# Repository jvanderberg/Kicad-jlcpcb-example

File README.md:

# JLCPCB KiCad Integration Example

This repository is a two layer 5V DC-DC power supply, created in KiCad and designed to integrate with JLCPCB. The power supply was just a test board I created, it should not be used for anything meaningful, but you could use this project as a template for new projects or just to test submitting to JCLPCB, and just delete the board unordered when you are done.

## Installing Libraries/Plugins

To get your local KiCad installation setup properly, open the Plugin and Content Manager.

1. Install the 'Fabrication Toolkit' Plugin from the KiCad official repository.

2. Install the 'impartGUI' Plugin from the KiCad official repository. Yes, that likely should be 'import GUI', but it's not.

3. In the Plugin and Content Manager, click the 'Manage...' button and add a new Repository with the URL: https://raw.githubusercontent.com/CDFER/cd_fer-kicad-repository/main/repository.json

4. Select 'CD_FER's KiCad repository' from the Repository drop down, select the 'Library' tab below, and then install 'JLCPCB KiCad Library'. Then 'Apply Changes'.

## Using 'JLCPCB KiCad Library'

'JLCPCB KiCad Library' integrates itself into KiCad as provider of 3rd party symbols and matching footprints for all of the JLCPCB basic and preferred parts and for some selected popular extended parts. Basic parts are the parts that don't cost extra month for 'Economic' PCB assembly. To use this library:

1. Open the schematic editor and select 'Place | Place Symbols'

2. Search for a part, for example '100nf', '10kΩ', 'jlcpcb schottky'. If you want to browse all of the JLCPCB parts search for 'jlcpcb'

3. Select a matching part from the 'PCM_JLCPCB\*' folder. The name of the folder will vary based on the type of part.

I tend to use this mostly for passive resistors and capacitors and use impartGUI for everything else.

## impartGUI Configuration

If you use impartGUI to import LCSC part numbers (LCSC is the JLCPCB part supplier), you will need to tell KiCad where to find the footprints and symbols that impartGUI manages.

1. From the schematic editor, select 'Preferences | Manage Symbol Libraries' and add either a Global or Project Specific library that points to the .kicad_sym file that impart GUI downloaded. For example, in this project, it's a project specific directory, with a path ${KIPRJMOD}/LCSC/EasyEDA.kicad_sym.

2. From the PCB editor, select 'Preferences | Manage Footprint Libraries' and add either a Global or a Project Specific Library that points to the EasyEDA.pretty directory that impart GUI manages. In this project it's ${KIPRJMOD}/LCSC/EasyEDA.pretty

3. Make sure the nickname of the Footprint library is 'EasyEDA', if it's not, integration between symbols and footprints will break.

If you use JLCPCB parts across more than one project and reuse the same parts, I'd recommend using a Global symbol and Global Footprint library.

## Using impart GUI

1. You access impartGUI from the PCB editor, using the 'Tools | External Plugins | impartGUI' menu.

2. You can find LCSC part numbers on the [LCSC Website](https://lcsc.com). Also give this new website a try: [LCSC Parts Search Tool](https://lcscpartsearchgit.streamlit.app/?embed_options=dark_theme). The Part number should start with a 'C', for example, 'C109322'.

3. Enter the part number in text box to the right of the 'Manual Import' button, select 'auto KiCad settings', and make sure your 'Library Save Location' matches the root directory of the footprint and symbol library configuration you provided earlier. This doesn't except any of the standard KiCad locations like ${KIPRJMOD}, so you will have to enter the whole path, for example /Users/myuser/Documents/Project/LCSC.

4. Then click 'Manual Import'. If you don't see any errors, it should tell you all of the files it downloaded and where it put them.

### If you see an error when running impartGUI

impart GUI can fail to install properly, it complained that the python library, easyeda2kicad was not installed when I first ran it.

Fixing missing python libraries on MacOS:

1. Find the KiCad.app, usually /Applications/KiCad/KiCad.app, but if different for yourself, note the difference and adjust the next step.
2. Launch a terminal window and issue the command:

    ```
    cd /Applications/KiCad/KiCad.app/Contents/Frameworks/Python.framework/Versions/Current/bin
    ```

3. Install the missing library
    ```
    ./pip3 install easyeda2kicad
    ```

### If 3D models are missing in the 3D view

If parts you downloaded using impartGUI are missing 3D models in the 3D view, select the part in the PCB editor, hit the 'e' key to edit, click on 3D models, edit the path, it should point to the EasyEDA.3dshapes that impartGUI manages. You can hard code the path, but it's recommended to use the project environmental variables like `${KIPRJMOD}` or `${KICAD9_3RD_PARTY}`.

## Using 'Fabrication Toolkit'

1. Complete your KiCad design, ensuring that all DRC checks pass and from the PCB editor select 'Tools | External Plugins | Fabrication Toolkit'

2. You are likely fine using the default options. Just click 'Generate'. This will produce a 'production' folder in your project directory.

3. Go to JLCPCB and click 'Order now' from their homepage.

4. Click 'Add Gerber File' and select the Project.zip file (it will be named for your project name) from your 'production' folder.

5. Wait for JLCPCB to process your gerber files and review the options. I usually accept all the defaults. Scroll down to 'PCB Assembly' and turn that option on. Make sure 'Economic' is available and selected. If your board is simple and small, it should be. If it's not it's likely you selected a more complex option from the list above, or just have a very complex board not eligible for economic assembly.

6. Click the 'Next' button on the right. From the top of the screen select the 'BOM' tab. Click 'Add BOM File' and upload the bom.csv file from the production directory.

7. Click 'Add CPL file' and upload the positions.csv file from the production directory.

8. Click 'Process BOM & CPL'

9. Review the BOM. Correct any errors. All of the parts should be found. If you have an unmatched component you can search for a replacement in the LCSC inventory, or go back to your project in KiCad to research what went wrong. Click 'Next' when you are done. If you still have unmatched parts you will be asked to confirm that you don't wish to place them (maybe you will hand solder a part you already have)

10. Review the PCB layout carefully paying specific attention to rotation. Click on every part on the right hand side list and review it in the 3D preview. Ensure it's rotated properly and positioned properly. ICs, connectors and polarized parts tend to have issues here. Hit the space bar to rotate a part, the arrow keys nudge a misaligned part. When you are done, click 'Next'.

11. Enter a Project description and save to cart.

You did it!

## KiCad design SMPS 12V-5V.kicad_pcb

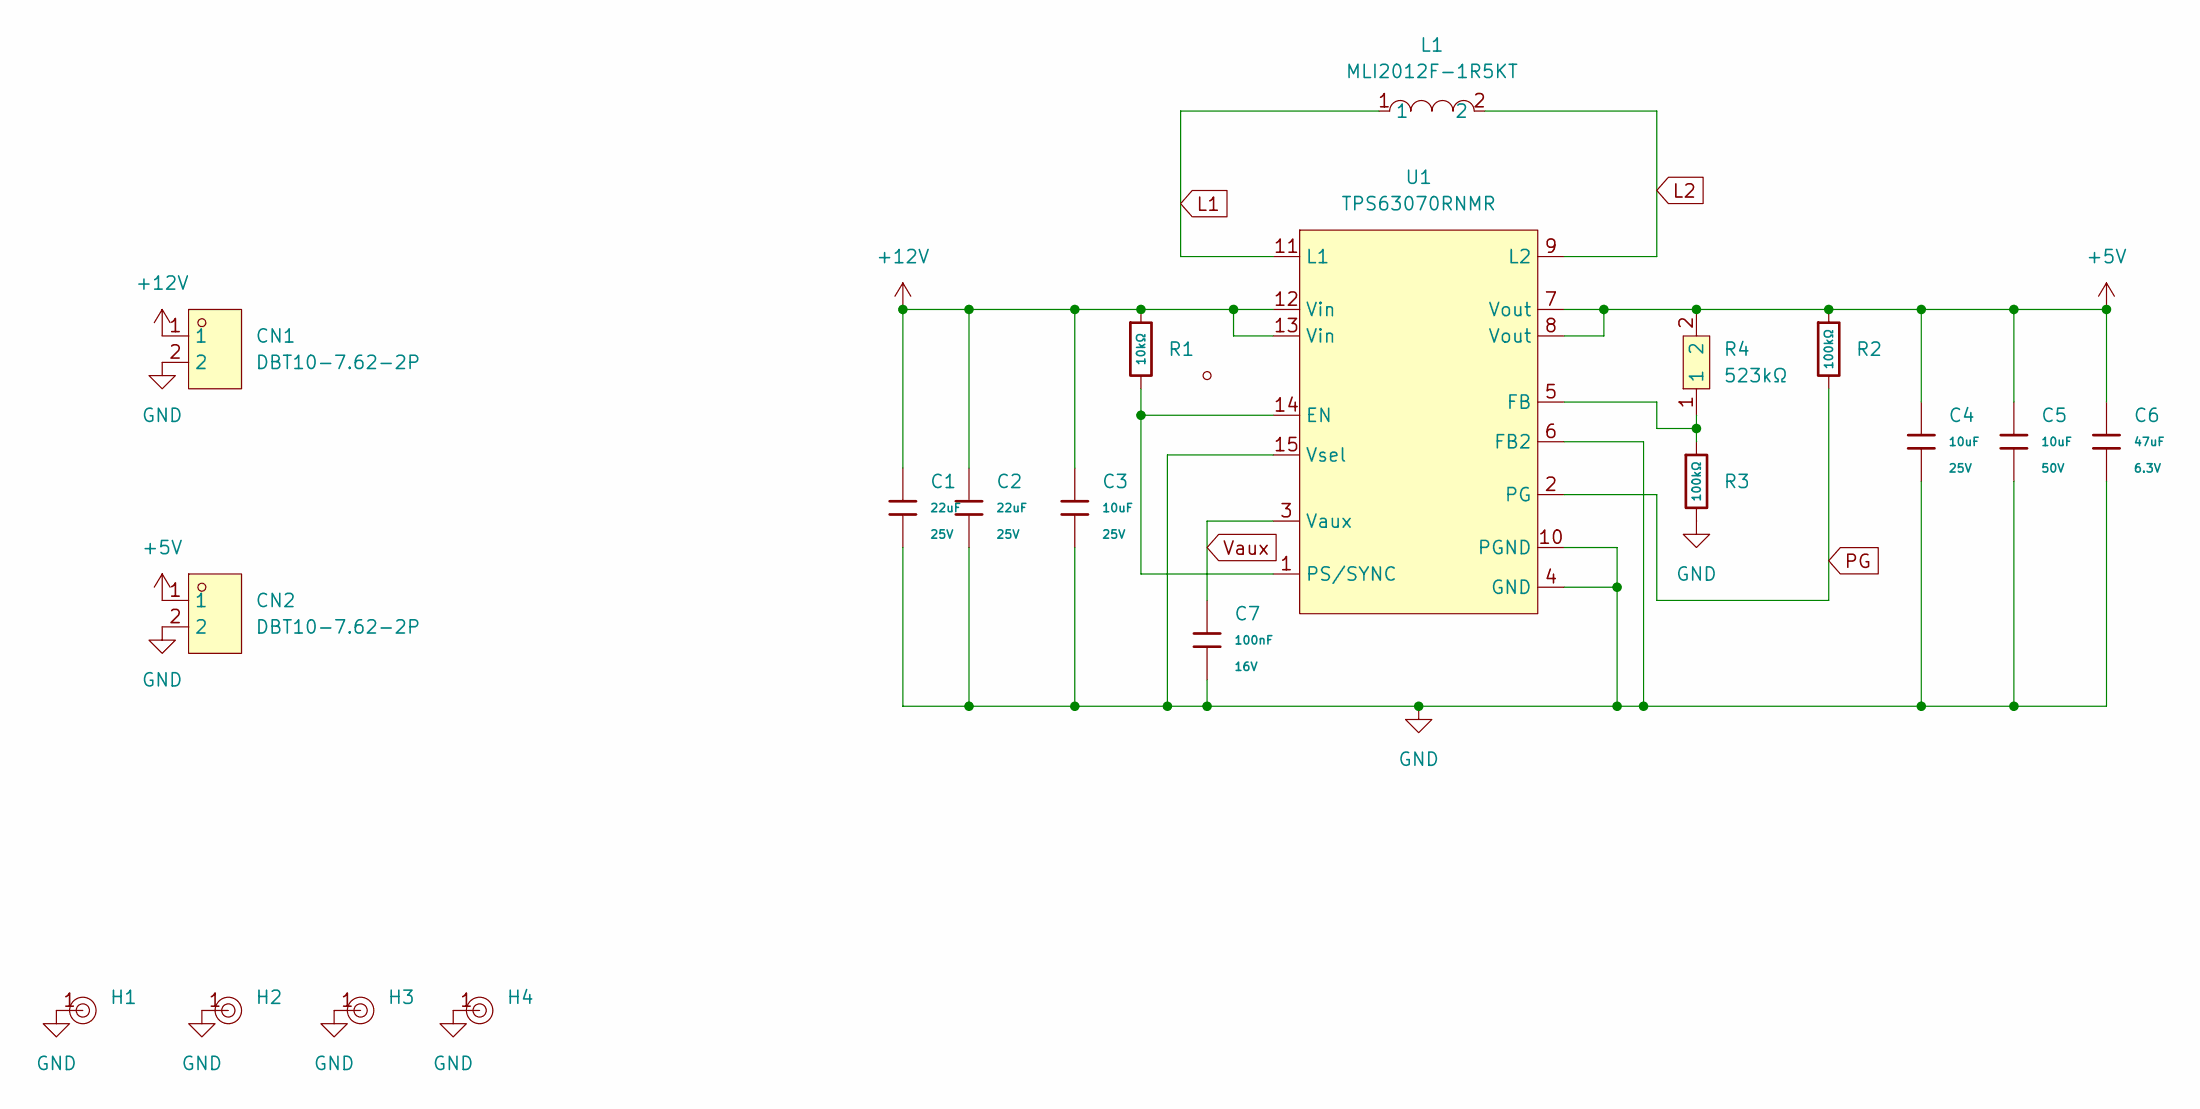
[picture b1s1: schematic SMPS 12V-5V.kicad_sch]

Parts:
C1, C2: 22uF; C_0805; Voltage Rated 25V; Tolerance ±20%; Part CL21A226MAQNNNE; LCSC C45783
C3, C4: 10uF; C_0603; Voltage Rated 25V; Tolerance ±20%; Part CL10A106MA8NRNC; LCSC C96446
C5: 10uF; C_0805; Voltage Rated 50V; Tolerance ±10%; Part GRM21BR61H106KE43L; LCSC C440198
C6: 47uF; C_0805; Voltage Rated 6.3V; Tolerance ±20%; Part CL21A476MQYNNNE; LCSC C16780
C7: 100nF; C_0402; Voltage Rated 16V; Tolerance ±10%; Part CL05B104KO5NNNC; LCSC C1525
CN1, CN2: DBT10-7.62-2P; CONN-TH_2P-P7.62_DBT10-7.62-2P; LCSC Part C395930
H1, H2, H3, H4: Hole, 3mm
L1: MLI2012F-1R5KT; L0805; LCSC Part C2885888
R1: 10kΩ; R_0603; Overload Voltage (Max) 75V; Tolerance ±1%; Part 0603WAF1002T5E; LCSC C25804
R2, R3: 100kΩ; R_0603; Overload Voltage (Max) 75V; Tolerance ±1%; Part 0603WAF1003T5E; LCSC C25803
R4: 523kΩ; R0805; LCSC Part C2683107
U1: TPS63070RNMR; VQFN-HR-15_L3.0-W2.5-P0.50-BL_TPS63070RNMR; LCSC Part C109322

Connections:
+5V: C4.1, C5.1, C6.1, CN2.1, R2.1, R4.2, U1.7 (Vout), U1.8 (Vout)
+12V: C1.1, C2.1, C3.1, CN1.1, R1.1, U1.12 (Vin), U1.13 (Vin)
GND: C1.2, C2.2, C3.2, C4.2, C5.2, C6.2, C7.2, CN1.2, CN2.2, H1.1, H2.1, H3.1, H4.1, R3.2, U1.4 (GND), U1.6 (FB2), U1.10 (PGND), U1.15 (Vsel)
L1: L1.1, U1.11 (L1)
L2: L1.2, U1.9 (L2)
unnamed: R1.2, U1.1 (PS/SYNC), U1.14 (EN)
unnamed: R3.1, R4.1, U1.5 (FB)
PG: R2.2, U1.2 (PG)
Vaux: C7.1, U1.3 (Vaux)

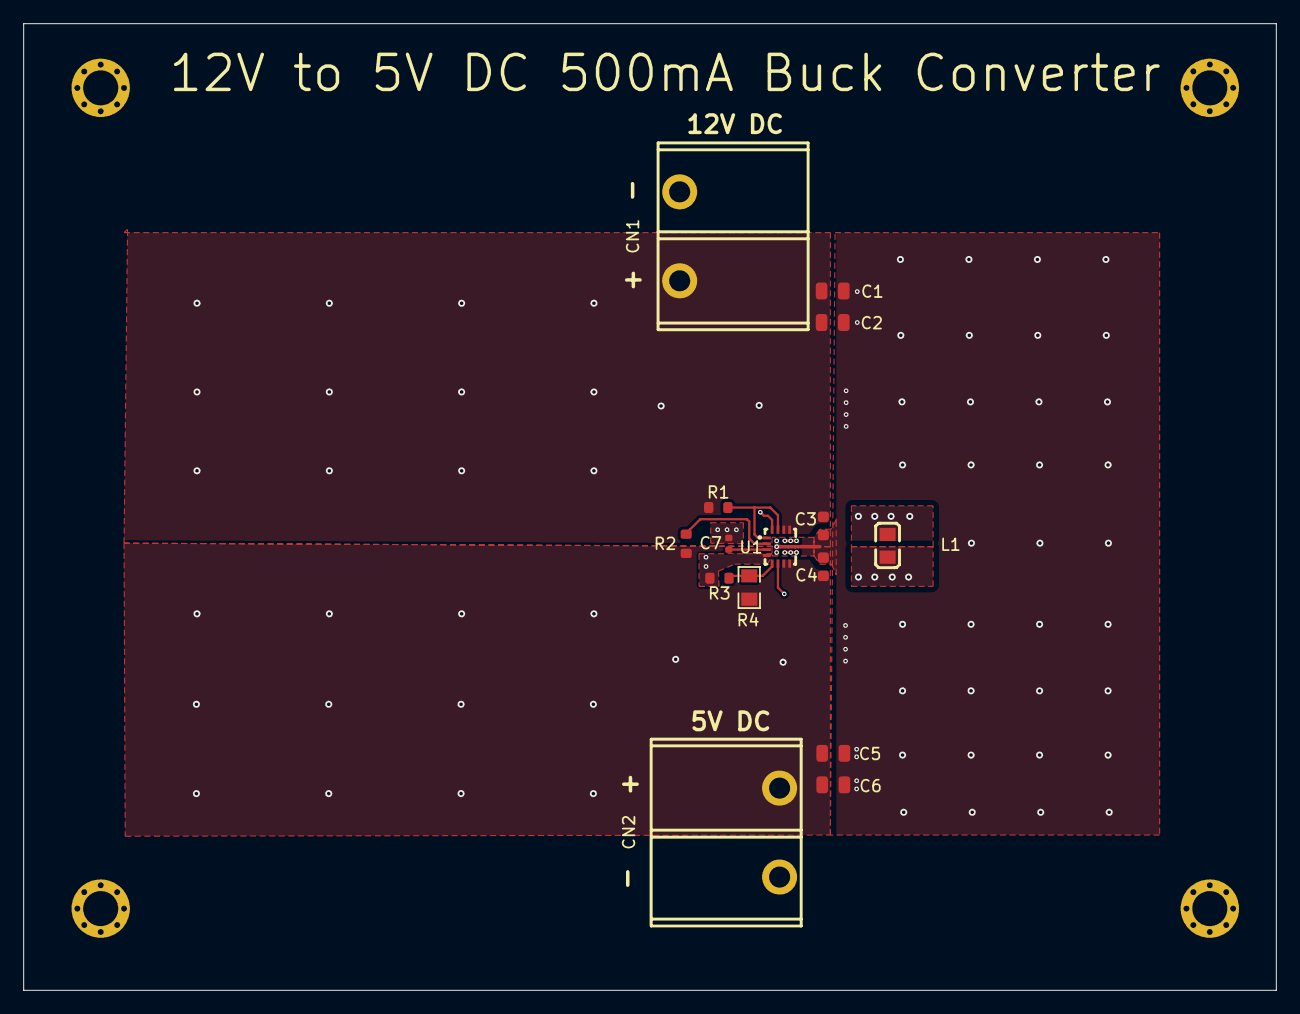
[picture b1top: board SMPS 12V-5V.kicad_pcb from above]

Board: 2 copper layers, 107.3 x 82.8 mm, 19 parts (0 on the bottom side), 9 nets.

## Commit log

2025-07-15 Created
2025-07-16 Readme update
2025-07-16 Readme
2025-08-04 Update README.md
    New Repository Repo URL is incorrect. The link ends with .js instead od .json
    It reads:
    In the Plugin and Content Manager, click the 'Manage...' button and add a new Repository with the URL: https://raw.githubusercontent.com/CDFER/cd_fer-kicad-repository/main/repository.js
    Corrected to:
    In the Plugin and Content Manager, click the 'Manage...' button and add a new Repository with the URL: https://raw.githubusercontent.com/CDFER/cd_fer-kicad-repository/main/repository.json
